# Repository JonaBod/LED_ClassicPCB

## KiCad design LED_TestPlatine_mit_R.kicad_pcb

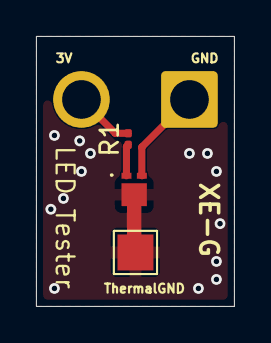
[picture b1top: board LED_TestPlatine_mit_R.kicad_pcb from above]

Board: 2 copper layers, 11.0 x 15.0 mm, 3 parts (0 on the bottom side), 2 nets.

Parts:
R1: 50; R_0201_0603Metric
ThermalGND: TestPoint_Pad_2.0x2.0mm
Y1: XEGARY-H2-0000-000-000000K2001; XEGARYH20000000000000K2001

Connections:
unnamed: R1.1, Y1.1 (A)
ThermalGround: ThermalGND.1, Y1.3 (EP)

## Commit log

2026-04-21 added new files for boards with resistors
2026-04-22 added resistor to respective files
2026-04-22 moved resistor to the correct board file
